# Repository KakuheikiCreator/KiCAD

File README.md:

# This is a project designed using KiCAD.
***

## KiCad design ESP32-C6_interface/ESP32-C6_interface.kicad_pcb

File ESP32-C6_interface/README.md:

# ESP32-C6 interface PCB
This is a PCB that uses ESP32-C6, LCD (AQM1602), and four buttons.

# Release History

| Version | Release Date | Overview |
| ---- | ---- | ---- |
| V1.0 | 2025/07/05 | New Creation |

# License
MIT License

# Photo

****

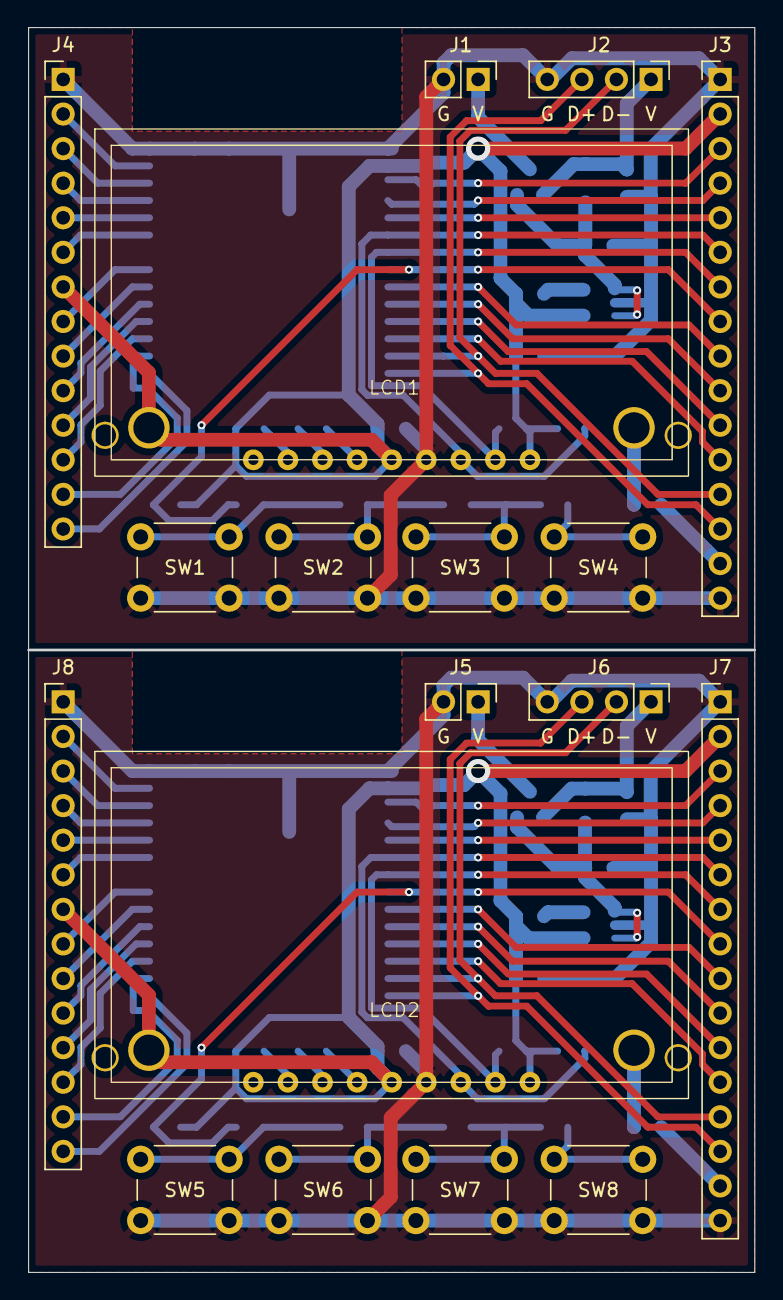
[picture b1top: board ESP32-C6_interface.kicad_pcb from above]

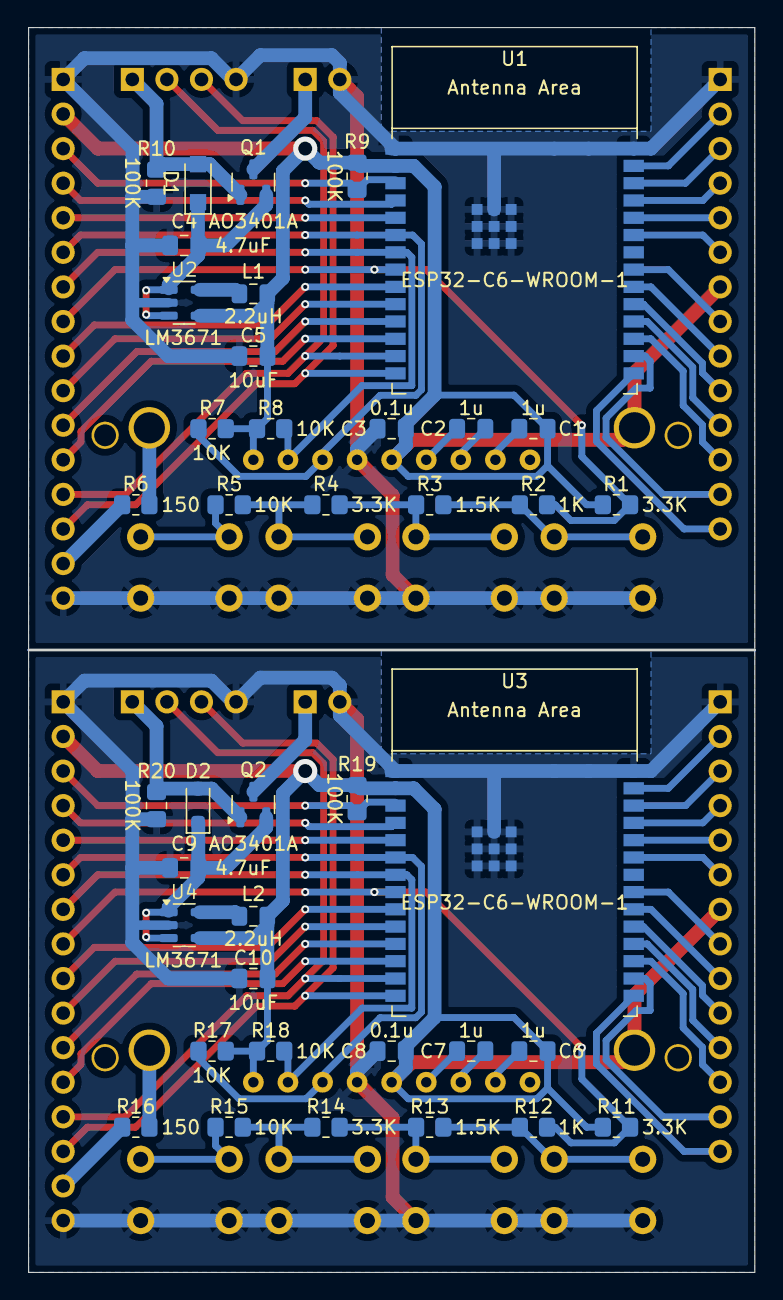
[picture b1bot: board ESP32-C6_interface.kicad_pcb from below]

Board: 2 copper layers, 53.3 x 91.3 mm, 58 parts (40 on the bottom side), 39 nets.

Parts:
C1, C2, C6, C7: 1u; C_0805_2012Metric_Pad1.18x1.45mm_HandSolder
C3, C8: 0.1u; C_0805_2012Metric_Pad1.18x1.45mm_HandSolder
C4, C9: 4.7uF; C_0805_2012Metric_Pad1.18x1.45mm_HandSolder
C5, C10: 10uF; C_0805_2012Metric_Pad1.18x1.45mm_HandSolder
D1: RB160M; Nexperia_CFP3_SOD-123W
D2: CUHS20S60; D_SOD-323_HandSoldering
J1, J5: Conn_01x02; PinHeader_1x02_P2.54mm_Vertical
J2, J6: Conn_01x04; PinHeader_1x04_P2.54mm_Vertical
J3, J7: Conn_01x16; PinHeader_1x16_P2.54mm_Vertical
J4, J8: Conn_01x14; PinHeader_1x14_P2.54mm_Vertical
L1, L2: 2.2uH; L_0805_2012Metric_Pad1.15x1.40mm_HandSolder
LCD1, LCD2: AQM1602Y; LCD_AQM1602Y
Q1, Q2: AO3401A; SOT-23
R1, R4, R11, R14: 3.3K; R_0805_2012Metric_Pad1.20x1.40mm_HandSolder
R2, R12: 1K; R_0805_2012Metric_Pad1.20x1.40mm_HandSolder
R3, R13: 1.5K; R_0805_2012Metric_Pad1.20x1.40mm_HandSolder
R5, R7, R8, R15, R17, R18: 10K; R_0805_2012Metric_Pad1.20x1.40mm_HandSolder
R6, R16: 150; R_0805_2012Metric_Pad1.20x1.40mm_HandSolder
R9, R10, R19, R20: 100K; R_0805_2012Metric_Pad1.20x1.40mm_HandSolder
SW1, SW2, SW3, SW4, SW5, SW6, SW7, SW8: SW_Push; SW_PUSH_6mm_H7.3mm
U1, U3: ESP32-C6-WROOM-1
U2, U4: LM3671

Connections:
+3V3: C1.1, C3.1, C5.1, C6.1, C8.1, C10.1, J3.2, J4.7, J7.2, J8.7, L1.2, L2.2, LCD1.5 (VDD), LCD1.9 (/RES), LCD1.A (Anode), LCD2.5 (VDD), LCD2.9 (/RES), LCD2.A (Anode), R1.1, R7.2, R8.2, R9.1, R11.1, R17.2, R18.2, R19.1, U1.2 (3V3), U2.4 (FB), U3.2 (3V3), U4.4 (FB)
+5V: D1.2 (A), D2.2 (A), J2.1, J6.1, Q1.1 (G), Q2.1 (G), R10.1, R20.1
+BATT: J1.1, J5.1, Q1.3 (D), Q2.3 (D)
A0: J3.8, J7.8, R1.2, R2.1, R11.2, R12.1, U1.8 (GPIO0/ADC1_CH0/XTAL_32K_P), U3.8 (GPIO0/ADC1_CH0/XTAL_32K_P)
EN: J3.3, J7.3, R9.2, R19.2, U1.3 (EN/CHIP_PU), U3.3 (EN/CHIP_PU)
GND: C3.2, C4.2, C5.2, C8.2, C9.2, C10.2, J1.2, J2.4, J3.1, J3.16, J4.1, J5.2, J6.4, J7.1, J7.16, J8.1, LCD1.6 (VSS), LCD2.6 (VSS), R10.2, R20.2, SW1.2, SW2.2, SW3.2, SW4.2, SW5.2, SW6.2, SW7.2, SW8.2, U1.1 (GND), U1.28 (GND), U1.29 (GND), U2.2 (GND), U3.1 (GND), U3.28 (GND), U3.29 (GND), U4.2 (GND)
I2C_SCL: J3.7, J7.7, LCD1.8 (SCL), LCD2.8 (SCL), R8.1, R18.1, U1.7 (MTDO/GPIO7), U3.7 (MTDO/GPIO7)
I2C_SDA: J3.6, J7.6, LCD1.7 (SDA), LCD2.7 (SDA), R7.1, R17.1, U1.6 (MTCK/GPIO6/ADC1_CH6), U3.6 (MTCK/GPIO6/ADC1_CH6)
IO1: J3.9, J7.9, U1.9 (GPIO1/ADC1_CH1/XTAL_32K_N), U3.9 (GPIO1/ADC1_CH1/XTAL_32K_N)
IO2: J4.2, J8.2, U1.27 (GPIO2/ADC1_CH2), U3.27 (GPIO2/ADC1_CH2)
IO3: J4.3, J8.3, U1.26 (GPIO3/ADC1_CH3), U3.26 (GPIO3/ADC1_CH3)
IO4: J3.4, J7.4, U1.4 (MTMS/GPIO4/ADC1_CH4), U3.4 (MTMS/GPIO4/ADC1_CH4)
IO5: J3.5, J7.5, U1.5 (MTDI/GPIO5/ADC1_CH5), U3.5 (MTDI/GPIO5/ADC1_CH5)
IO8: J3.10, J7.10, U1.10 (GPIO8), U3.10 (GPIO8)
IO9: J4.14, J8.14, U1.15 (GPIO9), U3.15 (GPIO9)
IO10: J3.11, J7.11, U1.11 (GPIO10), U3.11 (GPIO10)
IO11: J3.12, J7.12, U1.12 (GPIO11), U3.12 (GPIO11)
IO12: J2.2, J3.13, J6.2, J7.13, U1.13 (GPIO12/USB_D-), U3.13 (GPIO12/USB_D-)
IO13: J2.3, J3.14, J6.3, J7.14, U1.14 (GPIO13/USB_D+), U3.14 (GPIO13/USB_D+)
IO15: J4.6, J8.6, U1.23 (GPIO15), U3.23 (GPIO15)
IO18: J4.13, J8.13, U1.16 (GPIO18), U3.16 (GPIO18)
IO19: J4.12, J8.12, U1.17 (GPIO19), U3.17 (GPIO19)
IO20: J4.11, J8.11, U1.18 (GPIO20), U3.18 (GPIO20)
IO21: J4.10, J8.10, U1.19 (GPIO21), U3.19 (GPIO21)
IO22: J4.9, J8.9, U1.20 (GPIO22), U3.20 (GPIO22)
IO23: J4.8, J8.8, U1.21 (GPIO23), U3.21 (GPIO23)
LED_K: J3.15, J7.15, R6.2, R16.2
unnamed: C4.1, C9.1, D1.1 (K), D2.1 (K), Q1.2 (S), Q2.2 (S), U2.1 (Vin), U2.3 (EN), U4.1 (Vin), U4.3 (EN)
unnamed: C2.1, C7.1, LCD1.3 (CAP1N), LCD2.3 (CAP1N)
unnamed: C2.2, C7.2, LCD1.4 (CAP1P), LCD2.4 (CAP1P)
unnamed: LCD1.K (Cathode), LCD2.K (Cathode), R6.1, R16.1
unnamed: C1.2, C6.2, LCD1.2 (VOUT), LCD2.2 (VOUT)
unnamed: R2.2, R3.1, R12.2, R13.1, SW1.1, SW5.1
unnamed: R3.2, R4.1, R13.2, R14.1, SW2.1, SW6.1
unnamed: R4.2, R5.1, R14.2, R15.1, SW3.1, SW7.1
unnamed: R5.2, R15.2, SW4.1, SW8.1
unnamed: L1.1, L2.1, U2.5 (SW), U4.5 (SW)
U0_RXD: J4.5, J8.5, U1.24 (U0RXD/GPIO17), U3.24 (U0RXD/GPIO17)
U0_TXD: J4.4, J8.4, U1.25 (U0TXD/GPIO16), U3.25 (U0TXD/GPIO16)

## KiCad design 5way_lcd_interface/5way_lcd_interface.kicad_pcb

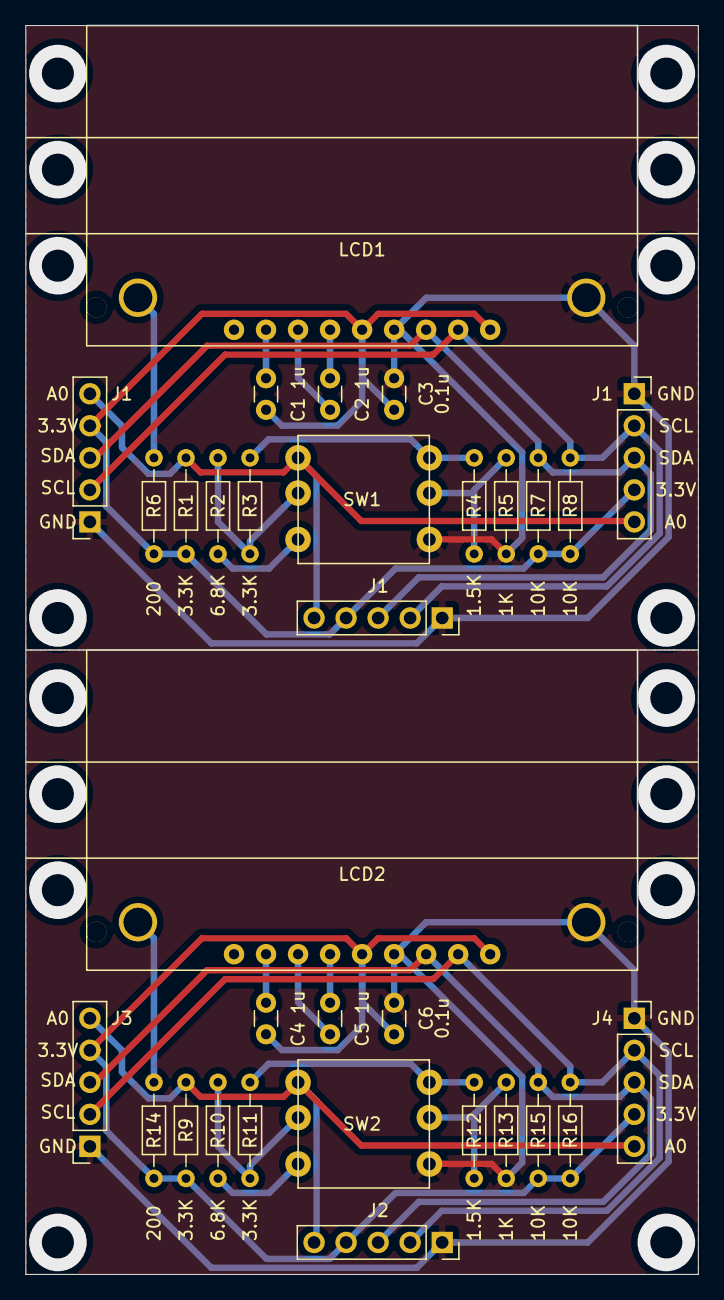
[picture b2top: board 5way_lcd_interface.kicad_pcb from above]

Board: 2 copper layers, 53.3 x 99.0 mm, 32 parts (0 on the bottom side), 13 nets.

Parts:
C1, C2, C4, C5: 1u; C_Disc_D3.0mm_W1.6mm_P2.50mm
C3, C6: 0.1u; C_Disc_D3.0mm_W1.6mm_P2.50mm
J1, J1#2, J1#3, J2, J3, J4: Conn_01x05; PinSocket_1x05_P2.54mm_Vertical
LCD1, LCD2: AQM1602Y
R1, R3, R9, R11: 3.3K; R_Axial_DIN0204_L3.6mm_D1.6mm_P7.62mm_Horizontal
R2, R10: 6.8K; R_Axial_DIN0204_L3.6mm_D1.6mm_P7.62mm_Horizontal
R4, R12: 1.5K; R_Axial_DIN0204_L3.6mm_D1.6mm_P7.62mm_Horizontal
R5, R13: 1K; R_Axial_DIN0204_L3.6mm_D1.6mm_P7.62mm_Horizontal
R6, R14: 200; R_Axial_DIN0204_L3.6mm_D1.6mm_P7.62mm_Horizontal
R7, R8, R15, R16: 10K; R_Axial_DIN0204_L3.6mm_D1.6mm_P7.62mm_Horizontal
SW1, SW2: SW_5WAY

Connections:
+3V3: C1.1, C3.1, C4.1, C6.1, J1.4, J1#2.4, J1#3.4, J2.4, J3.4, J4.4, LCD1.5, LCD1.9, LCD2.5, LCD2.9, R1.1, R6.1, R7.2, R8.2, R9.1, R14.1, R15.2, R16.2
A0: J1.5, J1#2.5, J1#3.5, J2.5, J3.5, J4.5, R1.2, R9.2, SW1.1, SW2.1
GND: C3.2, C6.2, J1.1, J1#2.1, J1#3.1, J2.1, J3.1, J4.1, LCD1.6, LCD1.K, LCD2.6, LCD2.K, R5.1, R13.1, SW1.4, SW2.4
unnamed: C1.2, C4.2, LCD1.2, LCD2.2
unnamed: C2.1, C5.1, LCD1.3, LCD2.3
unnamed: C2.2, C5.2, LCD1.4, LCD2.4
unnamed: J1.2, J1#2.2, J1#3.2, J2.2, J3.2, J4.2, LCD1.8, LCD2.8, R8.1, R16.1
unnamed: J1.3, J1#2.3, J1#3.3, J2.3, J3.3, J4.3, LCD1.7, LCD2.7, R7.1, R15.1
unnamed: LCD1.A, LCD2.A, R6.2, R14.2
unnamed: R2.1, R3.2, R10.1, R11.2, SW1.2, SW2.2
unnamed: R2.2, R10.2, SW1.3, SW2.3
unnamed: R3.1, R4.2, R11.1, R12.2, SW1.6, SW2.6
unnamed: R4.1, R5.2, R12.1, R13.2, SW1.5, SW2.5

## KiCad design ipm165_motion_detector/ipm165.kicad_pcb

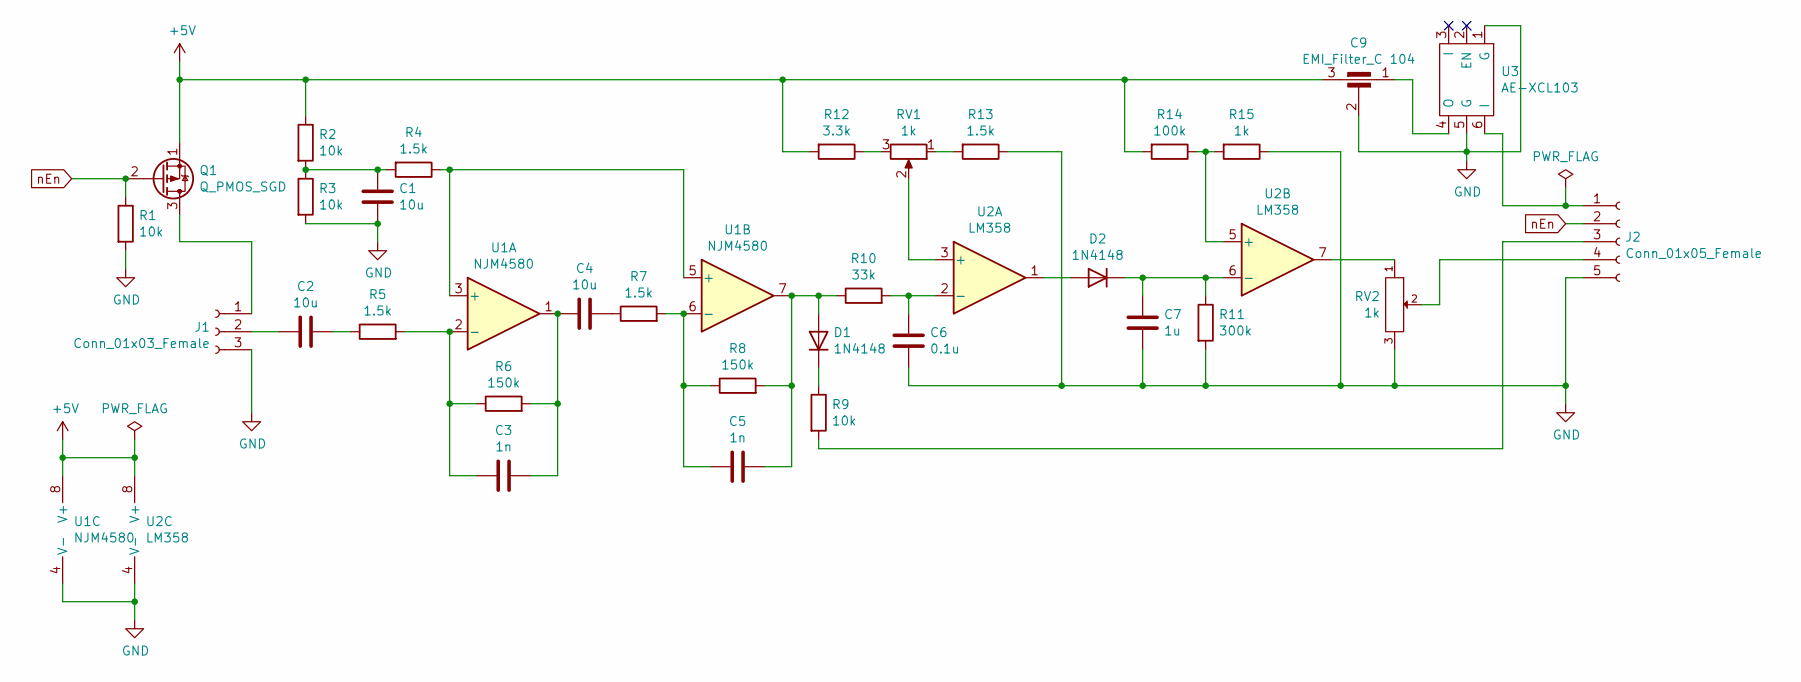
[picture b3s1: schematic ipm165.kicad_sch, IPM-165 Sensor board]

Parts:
C1, C2, C4: 10u; C_2
C3, C5: 1n; C_2
C6: 0.1u; C_2
C7: 1u; C_2
C9: EMI_Filter_C 104; TO-220_Filter
D1, D2: 1N4148; D_2
J1: Conn_01x03_Female; PinSocket_1x03_P2.54mm
J2: Conn_01x05_Female; JST_XH_S5B-XH-A_1x05_P2.50mm_Horizontal
Q1: Q_PMOS_SGD; TO-92_Inline_Wide
R1, R2, R3, R9: 10k; R_2
R4, R5, R7, R13: 1.5k; R_2
R6, R8: 150k; R_2
R10: 33k; R_2
R11: 300k; R_2
R12: 3.3k; R_2
R14: 100k; R_2
R15: 1k; R_2
RV1: 1k; JST_XH_S3B-XH-A_1x03_P2.50mm_Horizontal
RV2: 1k; Potentiometer_T73YP_Vertical
U1: NJM4580; DIP08
U2: LM358; DIP08
U3: AE-XCL103; DIP6

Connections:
+5V: C9.3, Q1.1 (S), R2.1, R12.2, R14.2, U1.8 (V+), U2.8 (V+)
GND: C1.2, C6.2, C7.2, C9.2, J1.3, J2.5, R1.2, R3.2, R11.2, R13.1, R15.1, RV2.3, U1.4 (V-), U2.4 (V-), U3.1 (G), U3.5 (G)
unnamed: C1.1, R2.2, R3.1, R4.2
unnamed: C2.1, J1.2
unnamed: C2.2, R5.1
unnamed: C3.1, R5.2, R6.1, U1.2 (-)
unnamed: C3.2, C4.1, R6.2, U1.1
unnamed: C4.2, R7.1
unnamed: C5.1, R7.2, R8.1, U1.6 (-)
unnamed: C5.2, D1.2 (A), R8.2, R10.1, U1.7
unnamed: C6.1, R10.2, U2.2 (-)
unnamed: C7.1, D2.1 (K), R11.1, U2.6 (-)
unnamed: C9.1, U3.4 (O)
unnamed: D1.1 (K), R9.1
unnamed: D2.2 (A), U2.1
unnamed: J1.1, Q1.3 (D)
unnamed: J2.1, U3.6 (I)
unnamed: J2.3, R9.2
unnamed: J2.4, RV2.2
unnamed: R4.1, U1.3 (+), U1.5 (+)
unnamed: R12.1, RV1.3
unnamed: R13.2, RV1.1
unnamed: R14.1, R15.2, U2.5 (+)
unnamed: RV1.2, U2.3 (+)
unnamed: RV2.1, U2.7
nEn: J2.2, Q1.2 (G), R1.1

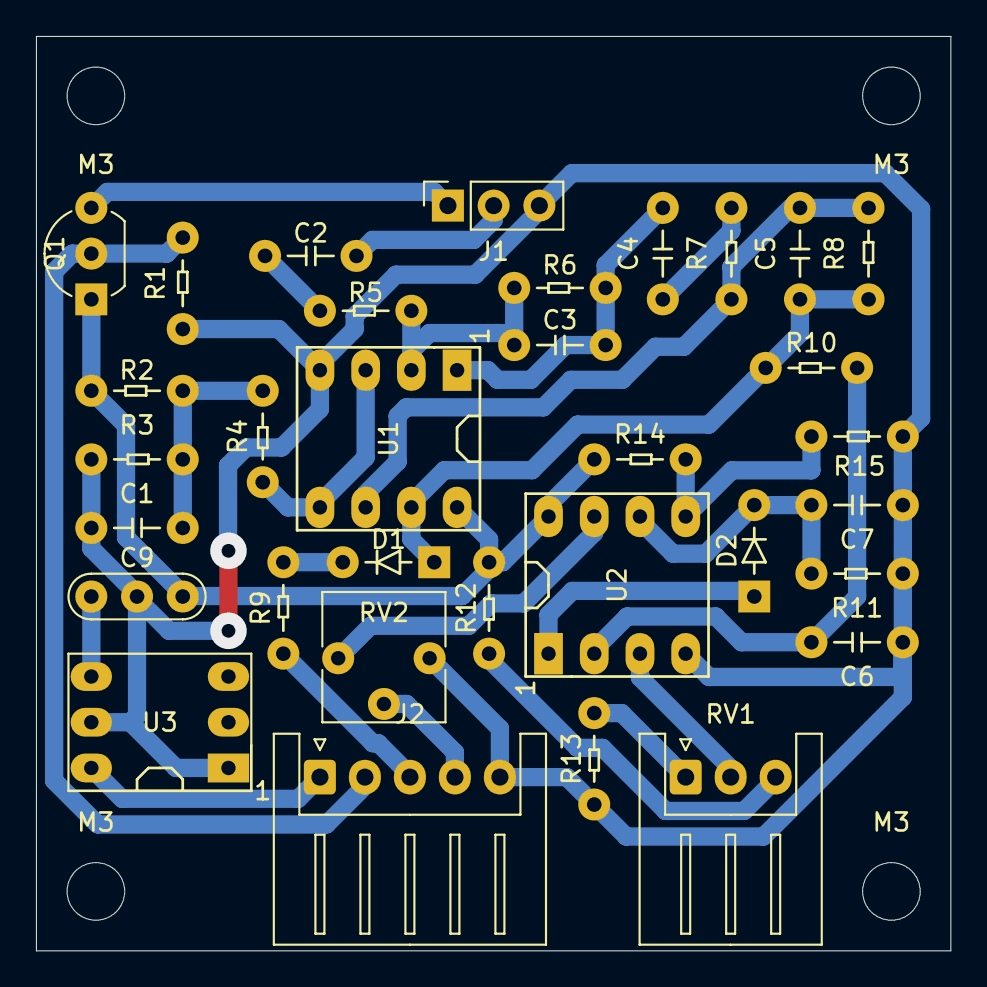
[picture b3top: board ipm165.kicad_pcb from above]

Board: 2 copper layers, 50.8 x 50.8 mm, 37 parts (0 on the bottom side), 26 nets.

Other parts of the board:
M3, M3#2, M3#3, M3#4: MountingHole_3.2mm_M3_ISO7380

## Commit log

2024-09-01 新規作成
2024-09-01 ライセンスの記述を更新
2025-07-05 Create a new PCB for ESP32-C6
2025-07-05 Add lisense
2025-07-05 Add description
2025-07-05 Add files via upload
    Actual board manufactured
